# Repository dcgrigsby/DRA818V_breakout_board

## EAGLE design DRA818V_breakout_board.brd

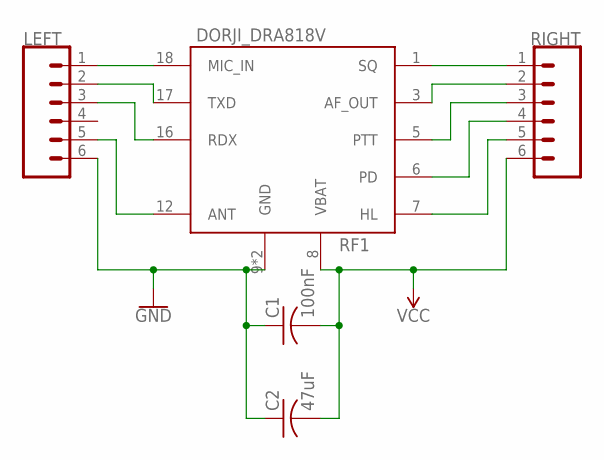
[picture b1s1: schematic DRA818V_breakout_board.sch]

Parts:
C1: 100nF; C0603
C2: 47uF; C0603
LEFT: CONN_06NO_SILK_FEMALE_PTH; 1X06_NO_SILK
RF1: DORJI_DRA818V
RIGHT: CONN_06NO_SILK_FEMALE_PTH; 1X06_NO_SILK

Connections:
GND: C1.1, C2.1, LEFT.6, RF1.9 (GND), RF1.10 (GND)
unnamed: RF1.7 (HL), RIGHT.5
unnamed: RF1.6 (PD), RIGHT.4
unnamed: RF1.5 (PTT), RIGHT.3
unnamed: RF1.3 (AF_OUT), RIGHT.2
unnamed: RF1.1 (SQ), RIGHT.1
unnamed: LEFT.5, RF1.12 (ANT)
unnamed: LEFT.1, RF1.18 (MIC_IN)
unnamed: LEFT.2, RF1.17 (TXD)
unnamed: LEFT.3, RF1.16 (RDX)
VCC: C1.2, C2.2, RF1.8 (VBAT), RIGHT.6

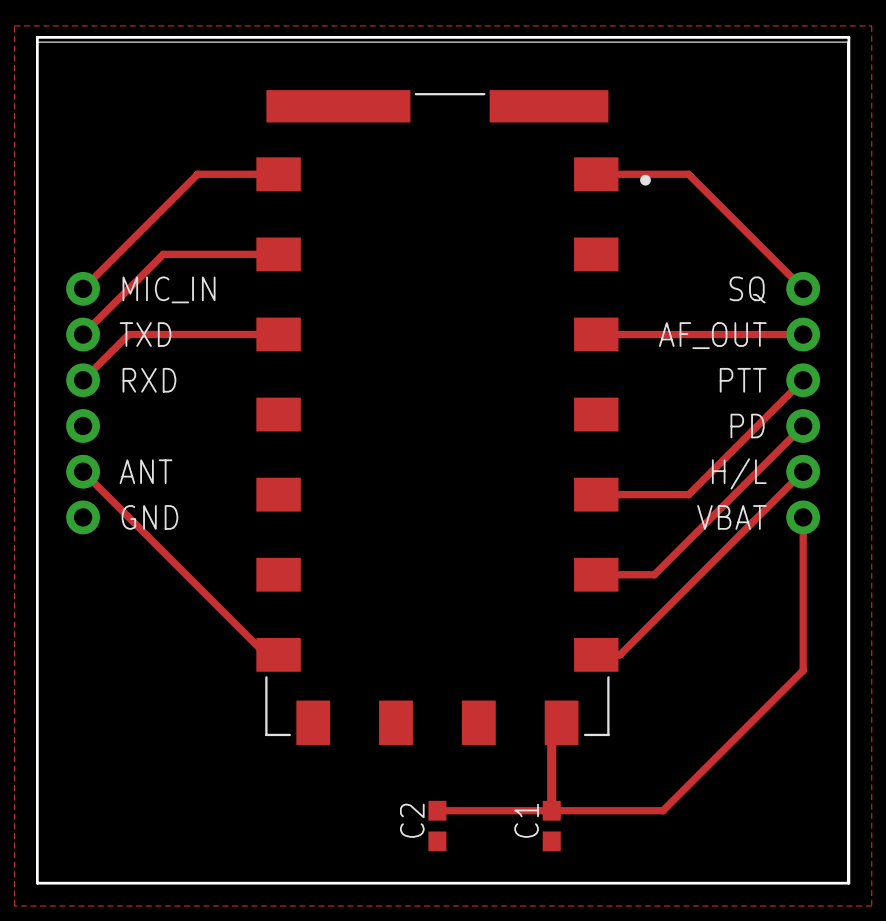
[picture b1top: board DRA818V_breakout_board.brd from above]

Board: 2 copper layers, 45.1 x 47.0 mm, 5 parts (0 on the bottom side), 11 nets.

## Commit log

2020-02-02 init

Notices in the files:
parts and their libraries:
SparkFun-Connectors: Licensing: Creative Commons ShareAlike 4.0 International - https://creativecommons.org/licenses/by-sa/4.0
